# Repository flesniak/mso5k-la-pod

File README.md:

Original version by Flemming Frandsen: https://gitlab.com/dren.dk/mso5k-la-pod

```
MMMMMMMM               MMMMMMMM   SSSSSSSSSSSSSSS      OOOOOOOOO     555555555555555555 kkkkkkkk                            LLLLLLLLLLL                            AAA
M:::::::M             M:::::::M SS:::::::::::::::S   OO:::::::::OO   5::::::::::::::::5 k::::::k                            L:::::::::L                           A:::A
M::::::::M           M::::::::MS:::::SSSSSS::::::S OO:::::::::::::OO 5::::::::::::::::5 k::::::k                            L:::::::::L                          A:::::A
M:::::::::M         M:::::::::MS:::::S     SSSSSSSO:::::::OOO:::::::O5:::::555555555555 k::::::k                            LL:::::::LL                         A:::::::A
M::::::::::M       M::::::::::MS:::::S            O::::::O   O::::::O5:::::5             k:::::k    kkkkkkk                   L:::::L                          A:::::::::A
M:::::::::::M     M:::::::::::MS:::::S            O:::::O     O:::::O5:::::5             k:::::k   k:::::k                    L:::::L                         A:::::A:::::A
M:::::::M::::M   M::::M:::::::M S::::SSSS         O:::::O     O:::::O5:::::5555555555    k:::::k  k:::::k                     L:::::L                        A:::::A A:::::A
M::::::M M::::M M::::M M::::::M  SS::::::SSSSS    O:::::O     O:::::O5:::::::::::::::5   k:::::k k:::::k    ---------------   L:::::L                       A:::::A   A:::::A
M::::::M  M::::M::::M  M::::::M    SSS::::::::SS  O:::::O     O:::::O555555555555:::::5  k::::::k:::::k     -:::::::::::::-   L:::::L                      A:::::A     A:::::A
M::::::M   M:::::::M   M::::::M       SSSSSS::::S O:::::O     O:::::O            5:::::5 k:::::::::::k      ---------------   L:::::L                     A:::::AAAAAAAAA:::::A
M::::::M    M:::::M    M::::::M            S:::::SO:::::O     O:::::O            5:::::5 k:::::::::::k                        L:::::L                    A:::::::::::::::::::::A
M::::::M     MMMMM     M::::::M            S:::::SO::::::O   O::::::O5555555     5:::::5 k::::::k:::::k                       L:::::L         LLLLLL    A:::::AAAAAAAAAAAAA:::::A
M::::::M               M::::::MSSSSSSS     S:::::SO:::::::OOO:::::::O5::::::55555::::::5k::::::k k:::::k                    LL:::::::LLLLLLLLL:::::L   A:::::A             A:::::A
M::::::M               M::::::MS::::::SSSSSS:::::S OO:::::::::::::OO  55:::::::::::::55 k::::::k  k:::::k                   L::::::::::::::::::::::L  A:::::A               A:::::A
M::::::M               M::::::MS:::::::::::::::SS    OO:::::::::OO      55:::::::::55   k::::::k   k:::::k                  L::::::::::::::::::::::L A:::::A                 A:::::A
MMMMMMMM               MMMMMMMM SSSSSSSSSSSSSSS        OOOOOOOOO          555555555     kkkkkkkk    kkkkkkk                 LLLLLLLLLLLLLLLLLLLLLLLLAAAAAAA                   AAAAAAA
```

This is a reimplementation of the Logic Analyzer pod for the Rigol MSO5000 scopes.

The scopes all come with the ability to accept a logic analyzer, all that's needed is a probe, this project is the implementation of the probe.

The schematic and PCB is in kicad 5 format.

# Sub-projects

There are a number of different projects each in its own subdir:

## lmh7324-16ch

* All 16 channels on a single board
* Uses 4x LMH7324 comparators
* Shows threshold voltage of each 8ch bank

## lmh7324-8ch

* 8 channel frontend pod
* On a 4 layer board
* With lmh7324 comparators
* And a simple volt-meter that shows the threshold voltage.

## breakout
* Board for converting the 2x25 2.54 mm pitch connector on the scope to two 2x13 pin 1.27 mm pitch connectors.

## panel-2019-03-20

* Panel produced in march.

## voltmeter

The firmware for the micro controller

# Unfinished experiments

## lmh7322
* 16 channel frontend pod
* Pretty close clone of the original
* One-sided load
* On a 4 layer board
* Direct 2x50 2.54mm ribbon connector to the scope
* Status: Done, except for silkscreen

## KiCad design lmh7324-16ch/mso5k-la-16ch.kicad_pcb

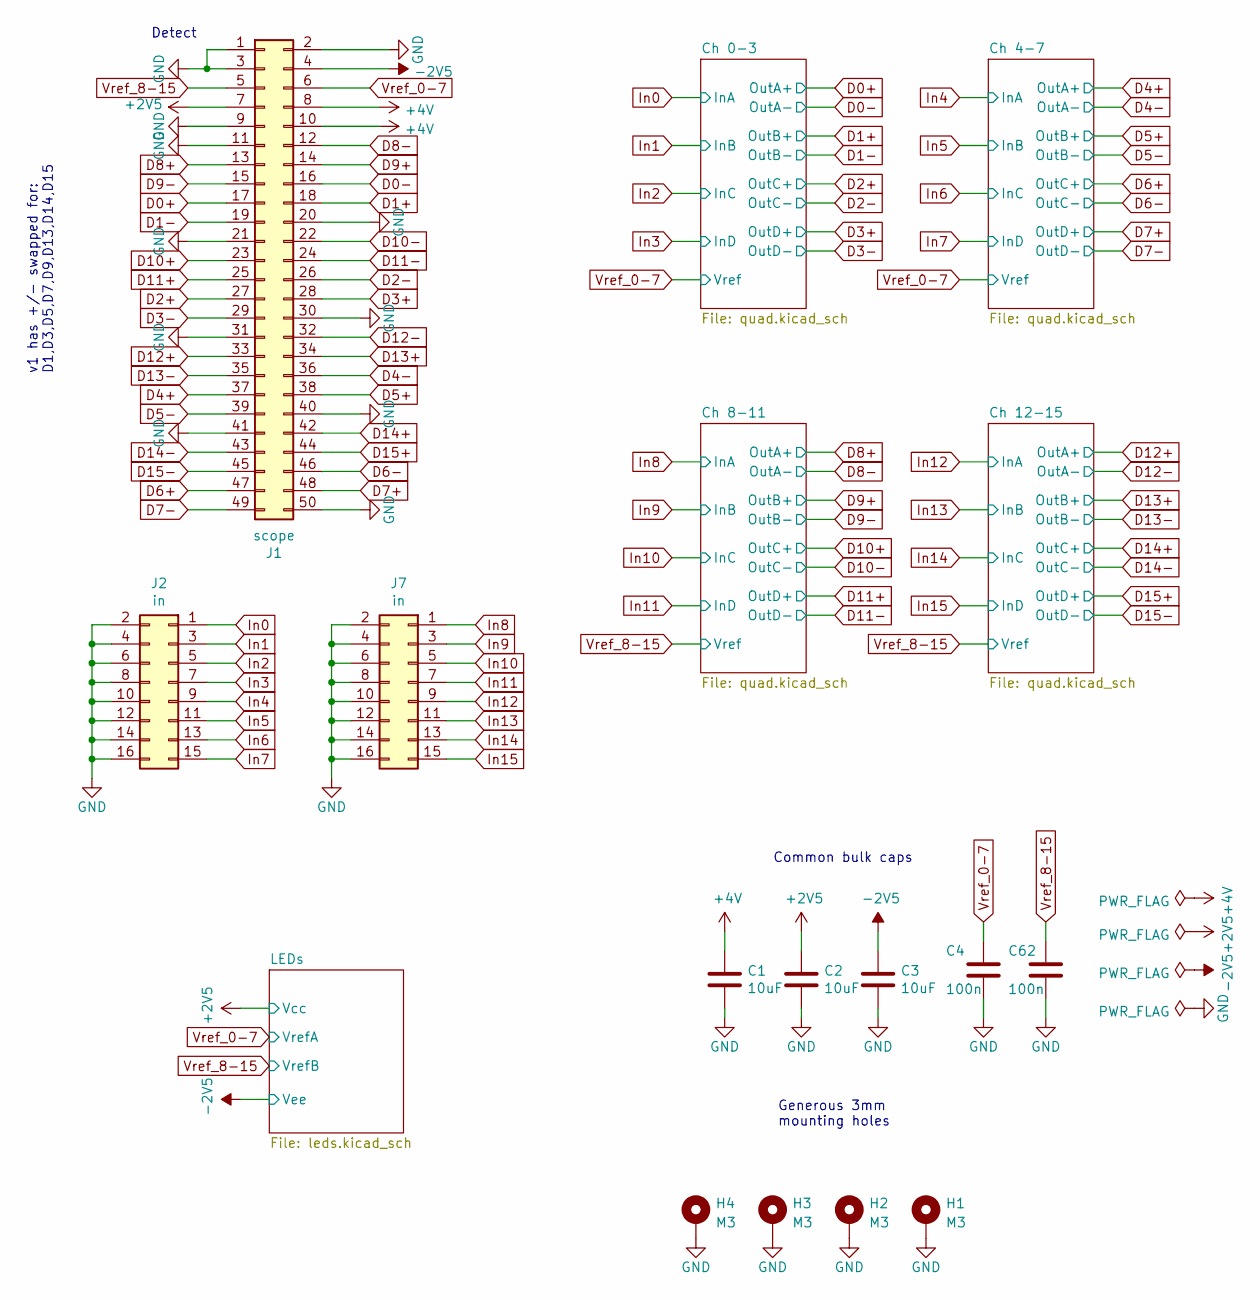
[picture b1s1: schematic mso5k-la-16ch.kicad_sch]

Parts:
C1, C2, C3: 10uF; C_0805_2012Metric
C4, C62: 100n; C_0603_1608Metric
H1, H2, H3, H4: M3; MountingHole_3.2mm_M3_Pad_Via
J1: scope; IDC-Header_2x25_P2.54mm_Vertical
J2, J7: in; PinSocket_2x08_P2.54mm_Vertical

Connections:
+2V5: C2.1, J1.7; also elsewhere on the board
+4V: C1.1, J1.8, J1.10; also elsewhere on the board
-2V5: C3.1, J1.4; also elsewhere on the board
D0+: J1.17; also elsewhere on the board
D0-: J1.16; also elsewhere on the board
D1+: J1.18; also elsewhere on the board
D1-: J1.19; also elsewhere on the board
D2+: J1.27; also elsewhere on the board
D2-: J1.26; also elsewhere on the board
D3+: J1.28; also elsewhere on the board
D3-: J1.29; also elsewhere on the board
D4+: J1.37; also elsewhere on the board
D4-: J1.36; also elsewhere on the board
D5+: J1.38; also elsewhere on the board
D5-: J1.39; also elsewhere on the board
D6+: J1.47; also elsewhere on the board
D6-: J1.46; also elsewhere on the board
D7+: J1.48; also elsewhere on the board
D7-: J1.49; also elsewhere on the board
D8+: J1.13; also elsewhere on the board
D8-: J1.12; also elsewhere on the board
D9+: J1.14; also elsewhere on the board
D9-: J1.15; also elsewhere on the board
D10+: J1.23; also elsewhere on the board
D10-: J1.22; also elsewhere on the board
D11+: J1.25; also elsewhere on the board
D11-: J1.24; also elsewhere on the board
D12+: J1.33; also elsewhere on the board
D12-: J1.32; also elsewhere on the board
D13+: J1.34; also elsewhere on the board
D13-: J1.35; also elsewhere on the board
D14+: J1.42; also elsewhere on the board
D14-: J1.43; also elsewhere on the board
D15+: J1.44; also elsewhere on the board
D15-: J1.45; also elsewhere on the board
GND: C1.2, C2.2, C3.2, C4.2, C62.2, H1.1, H2.1, H3.1, H4.1, J1.1, J1.2, J1.3, J1.9, J1.11, J1.20, J1.21, J1.30, J1.31, J1.40, J1.41, J1.50, J2.2, J2.4, J2.6, J2.8, J2.10, J2.12, J2.14, J2.16, J7.2, J7.4, J7.6, J7.8, J7.10, J7.12, J7.14, J7.16; also elsewhere on the board
In0: J2.1; also elsewhere on the board
In1: J2.3; also elsewhere on the board
In2: J2.5; also elsewhere on the board
In3: J2.7; also elsewhere on the board
In4: J2.9; also elsewhere on the board
In5: J2.11; also elsewhere on the board
In6: J2.13; also elsewhere on the board
In7: J2.15; also elsewhere on the board
In8: J7.1; also elsewhere on the board
In9: J7.3; also elsewhere on the board
In10: J7.5; also elsewhere on the board
In11: J7.7; also elsewhere on the board
In12: J7.9; also elsewhere on the board
In13: J7.11; also elsewhere on the board
In14: J7.13; also elsewhere on the board
In15: J7.15; also elsewhere on the board
Vref_0-7: C4.1, J1.6; also elsewhere on the board
Vref_8-15: C62.1, J1.5; also elsewhere on the board

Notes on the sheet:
Common bulk caps
v1 has +/- swapped for: D1,D3,D5,D7,D9,D13,D14,D15
Generous 3mm mounting holes
Detect

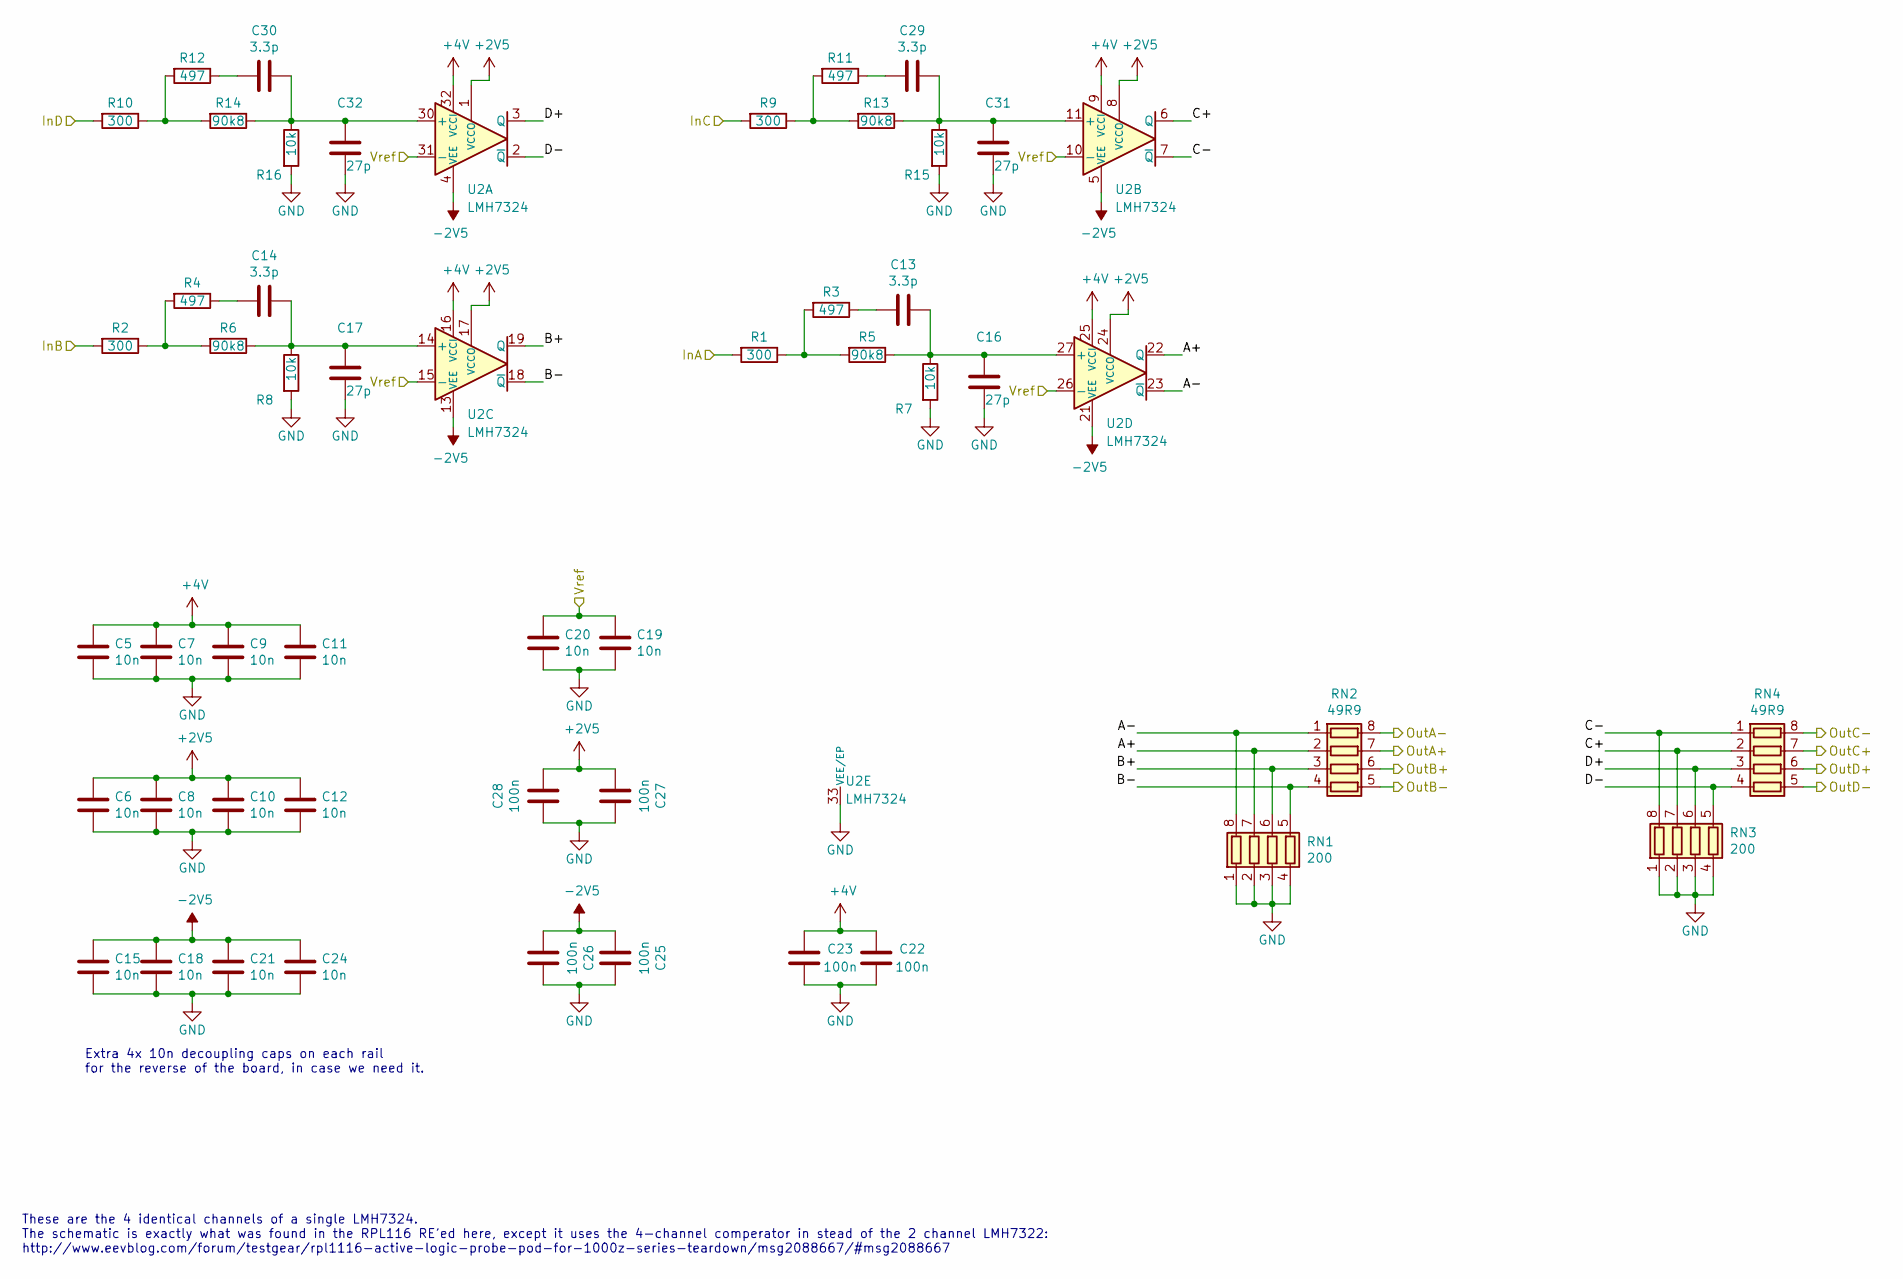
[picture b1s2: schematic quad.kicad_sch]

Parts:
C5, C6, C7, C8, C9, C10, C11, C12, C15, C18, C21, C24: 10n; C_0402_1005Metric
C13, C14, C29, C30: 3.3p; C_0603_1608Metric
C16, C17, C31, C32: 27p; C_0603_1608Metric
C19, C20: 10n; C_0603_1608Metric
C22, C23, C25, C26, C27, C28: 100n; C_0603_1608Metric
R1, R2, R9, R10: 300; R_0603_1608Metric
R3, R4, R11, R12: 497; R_0603_1608Metric
R5, R6, R13, R14: 90k8; R_0603_1608Metric
R7, R8, R15, R16: 10k; R_0603_1608Metric
RN1, RN3: 200; R_Array_Convex_4x0603
RN2, RN4: 49R9; R_Array_Convex_4x0603
U2: LMH7324; WQFN-32-1EP_5x5mm_P0.5mm_EP3.1x3.1mm

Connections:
+2V5: C6.1, C8.1, C10.1, C12.1, C27.2, C28.2, U2.1 (VCCO), U2.8 (VCCO), U2.17 (VCCO), U2.24 (VCCO); also elsewhere on the board
+4V: C5.1, C7.1, C9.1, C11.1, C22.1, C23.1, U2.9 (VCCI), U2.16 (VCCI), U2.25 (VCCI), U2.32 (VCCI); also elsewhere on the board
-2V5: C15.1, C18.1, C21.1, C24.1, C25.2, C26.2, U2.4 (VEE), U2.5 (VEE), U2.12 (VEE), U2.13 (VEE), U2.20 (VEE), U2.21 (VEE), U2.28 (VEE), U2.29 (VEE); also elsewhere on the board
/Ch 0-3/A+: RN1.7 (R2.2), RN2.2 (R2.1), U2.22 (Q)
/Ch 0-3/A-: RN1.8 (R1.2), RN2.1 (R1.1), U2.23 (~Q)
/Ch 0-3/B+: RN1.6 (R3.2), RN2.3 (R3.1), U2.19 (Q)
/Ch 0-3/B-: RN1.5 (R4.2), RN2.4 (R4.1), U2.18 (~Q)
/Ch 0-3/C+: RN3.7 (R2.2), RN4.2 (R2.1), U2.6 (Q)
/Ch 0-3/C-: RN3.8 (R1.2), RN4.1 (R1.1), U2.7 (~Q)
/Ch 0-3/D+: RN3.6 (R3.2), RN4.3 (R3.1), U2.3 (Q)
/Ch 0-3/D-: RN3.5 (R4.2), RN4.4 (R4.1), U2.2 (~Q)
D0+: RN2.7 (R2.2); also elsewhere on the board
D0-: RN2.8 (R1.2); also elsewhere on the board
D1+: RN2.6 (R3.2); also elsewhere on the board
D1-: RN2.5 (R4.2); also elsewhere on the board
D2+: RN4.7 (R2.2); also elsewhere on the board
D2-: RN4.8 (R1.2); also elsewhere on the board
D3+: RN4.6 (R3.2); also elsewhere on the board
D3-: RN4.5 (R4.2); also elsewhere on the board
GND: C5.2, C6.2, C7.2, C8.2, C9.2, C10.2, C11.2, C12.2, C15.2, C16.2, C17.2, C18.2, C19.2, C20.2, C21.2, C22.2, C23.2, C24.2, C25.1, C26.1, C27.1, C28.1, C31.2, C32.2, R7.2, R8.2, R15.2, R16.2, RN1.1 (R1.1), RN1.2 (R2.1), RN1.3 (R3.1), RN1.4 (R4.1), RN3.1 (R1.1), RN3.2 (R2.1), RN3.3 (R3.1), RN3.4 (R4.1), U2.33 (VEE/EP); also elsewhere on the board
In0: R1.2; also elsewhere on the board
In1: R2.2; also elsewhere on the board
In2: R9.2; also elsewhere on the board
In3: R10.2; also elsewhere on the board
unnamed: C13.2, R3.1
unnamed: C14.2, R4.1
unnamed: C29.2, R11.1
unnamed: C30.2, R12.1
unnamed: R1.1, R3.2, R5.2
unnamed: R2.1, R4.2, R6.2
unnamed: R10.1, R12.2, R14.2
unnamed: R9.1, R11.2, R13.2
unnamed: C30.1, C32.1, R14.1, R16.1, U2.30 (+)
unnamed: C29.1, C31.1, R13.1, R15.1, U2.11 (+)
unnamed: C14.1, C17.1, R6.1, R8.1, U2.14 (+)
unnamed: C13.1, C16.1, R5.1, R7.1, U2.27 (+)
Vref_0-7: C19.1, C20.1, U2.10 (-), U2.15 (-), U2.26 (-), U2.31 (-); also elsewhere on the board

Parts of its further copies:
C33, C34, C35, C36, C37, C38, C39, C40, C43, C46, C49, C52, C63, C64, C65, C66, C67, C68, C69, C70, C71, C74, C75, C76, C91, C92, C93, C94, C95, C96, C97, C98, C99, C102, C103, C104: 10n; C_0402_1005Metric
C41, C42, C57, C58, C72, C73, C87, C88, C100, C101, C115, C116: 3.3p; C_0603_1608Metric
C44, C45, C59, C60, C77, C78, C89, C90, C105, C106, C117, C118: 27p; C_0603_1608Metric
C47, C48, C79, C82, C107, C110: 10n; C_0603_1608Metric
C50, C51, C53, C54, C55, C56, C80, C81, C83, C84, C85, C86, C108, C109, C111, C112, C113, C114: 100n; C_0603_1608Metric
R17, R18, R25, R26, R38, R39, R46, R47, R54, R55, R62, R63: 300; R_0603_1608Metric
R19, R20, R27, R28, R40, R41, R48, R49, R56, R57, R64, R65: 497; R_0603_1608Metric
R21, R22, R29, R30, R42, R43, R50, R51, R58, R59, R66, R67: 90k8; R_0603_1608Metric
R23, R24, R31, R32, R44, R45, R52, R53, R60, R61, R68, R69: 10k; R_0603_1608Metric
RN5, RN7, RN9, RN11, RN13, RN15: 200; R_Array_Convex_4x0603
RN6, RN8, RN10, RN12, RN14, RN16: 49R9; R_Array_Convex_4x0603
U3, U4, U5: LMH7324; WQFN-32-1EP_5x5mm_P0.5mm_EP3.1x3.1mm

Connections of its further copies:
+2V5: C34.1, C36.1, C38.1, C40.1, C55.2, C56.2, C64.1, C67.1, C70.1, C75.1, C80.2, C83.2, C92.1, C95.1, C98.1, C103.1, C108.2, C111.2, U3.1 (VCCO), U3.8 (VCCO), U3.17 (VCCO), U3.24 (VCCO), U4.1 (VCCO), U4.8 (VCCO), U4.17 (VCCO), U4.24 (VCCO), U5.1 (VCCO), U5.8 (VCCO), U5.17 (VCCO), U5.24 (VCCO); also elsewhere on the board
+4V: C33.1, C35.1, C37.1, C39.1, C50.1, C51.1, C63.1, C66.1, C69.1, C74.1, C85.1, C86.1, C91.1, C94.1, C97.1, C102.1, C113.1, C114.1, U3.9 (VCCI), U3.16 (VCCI), U3.25 (VCCI), U3.32 (VCCI), U4.9 (VCCI), U4.16 (VCCI), U4.25 (VCCI), U4.32 (VCCI), U5.9 (VCCI), U5.16 (VCCI), U5.25 (VCCI), U5.32 (VCCI); also elsewhere on the board
-2V5: C43.1, C46.1, C49.1, C52.1, C53.2, C54.2, C65.1, C68.1, C71.1, C76.1, C81.2, C84.2, C93.1, C96.1, C99.1, C104.1, C109.2, C112.2, U3.4 (VEE), U3.5 (VEE), U3.12 (VEE), U3.13 (VEE), U3.20 (VEE), U3.21 (VEE), U3.28 (VEE), U3.29 (VEE), U4.4 (VEE), U4.5 (VEE), U4.12 (VEE), U4.13 (VEE), U4.20 (VEE), U4.21 (VEE), U4.28 (VEE), U4.29 (VEE), U5.4 (VEE), U5.5 (VEE), U5.12 (VEE), U5.13 (VEE), U5.20 (VEE), U5.21 (VEE), U5.28 (VEE), U5.29 (VEE); also elsewhere on the board
/Ch 4-7/A+: RN5.7 (R2.2), RN6.2 (R2.1), U3.22 (Q)
/Ch 4-7/A-: RN5.8 (R1.2), RN6.1 (R1.1), U3.23 (~Q)
/Ch 4-7/B+: RN5.6 (R3.2), RN6.3 (R3.1), U3.19 (Q)
/Ch 4-7/B-: RN5.5 (R4.2), RN6.4 (R4.1), U3.18 (~Q)
/Ch 4-7/C+: RN7.7 (R2.2), RN8.2 (R2.1), U3.6 (Q)
/Ch 4-7/C-: RN7.8 (R1.2), RN8.1 (R1.1), U3.7 (~Q)
/Ch 4-7/D+: RN7.6 (R3.2), RN8.3 (R3.1), U3.3 (Q)
/Ch 4-7/D-: RN7.5 (R4.2), RN8.4 (R4.1), U3.2 (~Q)
/Ch 8-11/A+: RN9.7 (R2.2), RN10.2 (R2.1), U4.22 (Q)
/Ch 8-11/A-: RN9.8 (R1.2), RN10.1 (R1.1), U4.23 (~Q)
/Ch 8-11/B+: RN9.6 (R3.2), RN10.3 (R3.1), U4.19 (Q)
/Ch 8-11/B-: RN9.5 (R4.2), RN10.4 (R4.1), U4.18 (~Q)
/Ch 8-11/C+: RN11.7 (R2.2), RN12.2 (R2.1), U4.6 (Q)
/Ch 8-11/C-: RN11.8 (R1.2), RN12.1 (R1.1), U4.7 (~Q)
/Ch 8-11/D+: RN11.6 (R3.2), RN12.3 (R3.1), U4.3 (Q)
/Ch 8-11/D-: RN11.5 (R4.2), RN12.4 (R4.1), U4.2 (~Q)
/Ch 12-15/A+: RN13.7 (R2.2), RN14.2 (R2.1), U5.22 (Q)
/Ch 12-15/A-: RN13.8 (R1.2), RN14.1 (R1.1), U5.23 (~Q)
/Ch 12-15/B+: RN13.6 (R3.2), RN14.3 (R3.1), U5.19 (Q)
/Ch 12-15/B-: RN13.5 (R4.2), RN14.4 (R4.1), U5.18 (~Q)
/Ch 12-15/C+: RN15.7 (R2.2), RN16.2 (R2.1), U5.6 (Q)
/Ch 12-15/C-: RN15.8 (R1.2), RN16.1 (R1.1), U5.7 (~Q)
/Ch 12-15/D+: RN15.6 (R3.2), RN16.3 (R3.1), U5.3 (Q)
/Ch 12-15/D-: RN15.5 (R4.2), RN16.4 (R4.1), U5.2 (~Q)
D4+: RN6.7 (R2.2); also elsewhere on the board
D4-: RN6.8 (R1.2); also elsewhere on the board
D5+: RN6.6 (R3.2); also elsewhere on the board
D5-: RN6.5 (R4.2); also elsewhere on the board
D6+: RN8.7 (R2.2); also elsewhere on the board
D6-: RN8.8 (R1.2); also elsewhere on the board
D7+: RN8.6 (R3.2); also elsewhere on the board
D7-: RN8.5 (R4.2); also elsewhere on the board
D8+: RN10.7 (R2.2); also elsewhere on the board
D8-: RN10.8 (R1.2); also elsewhere on the board
D9+: RN10.6 (R3.2); also elsewhere on the board
D9-: RN10.5 (R4.2); also elsewhere on the board
D10+: RN12.7 (R2.2); also elsewhere on the board
D10-: RN12.8 (R1.2); also elsewhere on the board
D11+: RN12.6 (R3.2); also elsewhere on the board
D11-: RN12.5 (R4.2); also elsewhere on the board
D12+: RN14.7 (R2.2); also elsewhere on the board
D12-: RN14.8 (R1.2); also elsewhere on the board
D13+: RN14.6 (R3.2); also elsewhere on the board
D13-: RN14.5 (R4.2); also elsewhere on the board
D14+: RN16.7 (R2.2); also elsewhere on the board
D14-: RN16.8 (R1.2); also elsewhere on the board
D15+: RN16.6 (R3.2); also elsewhere on the board
D15-: RN16.5 (R4.2); also elsewhere on the board
GND: C33.2, C34.2, C35.2, C36.2, C37.2, C38.2, C39.2, C40.2, C43.2, C44.2, C45.2, C46.2, C47.2, C48.2, C49.2, C50.2, C51.2, C52.2, C53.1, C54.1, C55.1, C56.1, C59.2, C60.2, C63.2, C64.2, C65.2, C66.2, C67.2, C68.2, C69.2, C70.2, C71.2, C74.2, C75.2, C76.2, C77.2, C78.2, C79.2, C80.1, C81.1, C82.2, C83.1, C84.1, C85.2, C86.2, C89.2, C90.2, C91.2, C92.2, C93.2, C94.2, C95.2, C96.2, C97.2, C98.2, C99.2, C102.2, C103.2, C104.2, C105.2, C106.2, C107.2, C108.1, C109.1, C110.2, C111.1, C112.1, C113.2, C114.2, C117.2, C118.2, R23.2, R24.2, R31.2, R32.2, R44.2, R45.2, R52.2, R53.2, R60.2, R61.2, R68.2, R69.2, RN5.1 (R1.1), RN5.2 (R2.1), RN5.3 (R3.1), RN5.4 (R4.1), RN7.1 (R1.1), RN7.2 (R2.1), RN7.3 (R3.1), RN7.4 (R4.1), RN9.1 (R1.1), RN9.2 (R2.1), RN9.3 (R3.1), RN9.4 (R4.1), RN11.1 (R1.1), RN11.2 (R2.1), RN11.3 (R3.1), RN11.4 (R4.1), RN13.1 (R1.1), RN13.2 (R2.1), RN13.3 (R3.1), RN13.4 (R4.1), RN15.1 (R1.1), RN15.2 (R2.1), RN15.3 (R3.1), RN15.4 (R4.1), U3.33 (VEE/EP), U4.33 (VEE/EP), U5.33 (VEE/EP); also elsewhere on the board
In4: R17.2; also elsewhere on the board
In5: R18.2; also elsewhere on the board
In6: R25.2; also elsewhere on the board
In7: R26.2; also elsewhere on the board
In8: R46.2; also elsewhere on the board
In9: R39.2; also elsewhere on the board
In10: R47.2; also elsewhere on the board
In11: R38.2; also elsewhere on the board
In12: R62.2; also elsewhere on the board
In13: R55.2; also elsewhere on the board
In14: R63.2; also elsewhere on the board
In15: R54.2; also elsewhere on the board
unnamed: C41.2, R19.1
unnamed: C42.2, R20.1
unnamed: C57.2, R27.1
unnamed: C58.2, R28.1
unnamed: C72.2, R40.1
unnamed: C73.2, R41.1
unnamed: C87.2, R48.1
unnamed: C88.2, R49.1
unnamed: C100.2, R56.1
unnamed: C101.2, R57.1
unnamed: C115.2, R64.1
unnamed: C116.2, R65.1
unnamed: R17.1, R19.2, R21.2
unnamed: R18.1, R20.2, R22.2
unnamed: R25.1, R27.2, R29.2
unnamed: R26.1, R28.2, R30.2
unnamed: R38.1, R40.2, R42.2
unnamed: R39.1, R41.2, R43.2
unnamed: R46.1, R48.2, R50.2
unnamed: R47.1, R49.2, R51.2
unnamed: R54.1, R56.2, R58.2
unnamed: R55.1, R57.2, R59.2
unnamed: R62.1, R64.2, R66.2
unnamed: R63.1, R65.2, R67.2
unnamed: C58.1, C60.1, R30.1, R32.1, U3.30 (+)
unnamed: C57.1, C59.1, R29.1, R31.1, U3.11 (+)
unnamed: C42.1, C45.1, R22.1, R24.1, U3.14 (+)
unnamed: C41.1, C44.1, R21.1, R23.1, U3.27 (+)
unnamed: C72.1, C77.1, R42.1, R44.1, U4.30 (+)
unnamed: C88.1, C90.1, R51.1, R53.1, U4.11 (+)
unnamed: C73.1, C78.1, R43.1, R45.1, U4.14 (+)
unnamed: C87.1, C89.1, R50.1, R52.1, U4.27 (+)
unnamed: C100.1, C105.1, R58.1, R60.1, U5.30 (+)
unnamed: C116.1, C118.1, R67.1, R69.1, U5.11 (+)
unnamed: C101.1, C106.1, R59.1, R61.1, U5.14 (+)
unnamed: C115.1, C117.1, R66.1, R68.1, U5.27 (+)
Vref_0-7: C47.1, C48.1, U3.10 (-), U3.15 (-), U3.26 (-), U3.31 (-); also elsewhere on the board
Vref_8-15: C79.1, C82.1, C107.1, C110.1, U4.10 (-), U4.15 (-), U4.26 (-), U4.31 (-), U5.10 (-), U5.15 (-), U5.26 (-), U5.31 (-); also elsewhere on the board

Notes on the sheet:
Extra 4x 10n decoupling caps on each rail for the reverse of the board, in case we need it.
These are the 4 identical channels of a single LMH7324. The schematic is exactly what was found in the RPL116 RE'ed here, except it uses the 4-channel comperator in stead of the 2 channel LMH7322: http://www.eevblog.com/forum/testgear/rpl1116-active-logic-probe-pod-for-1000z-series-teardown/msg2088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

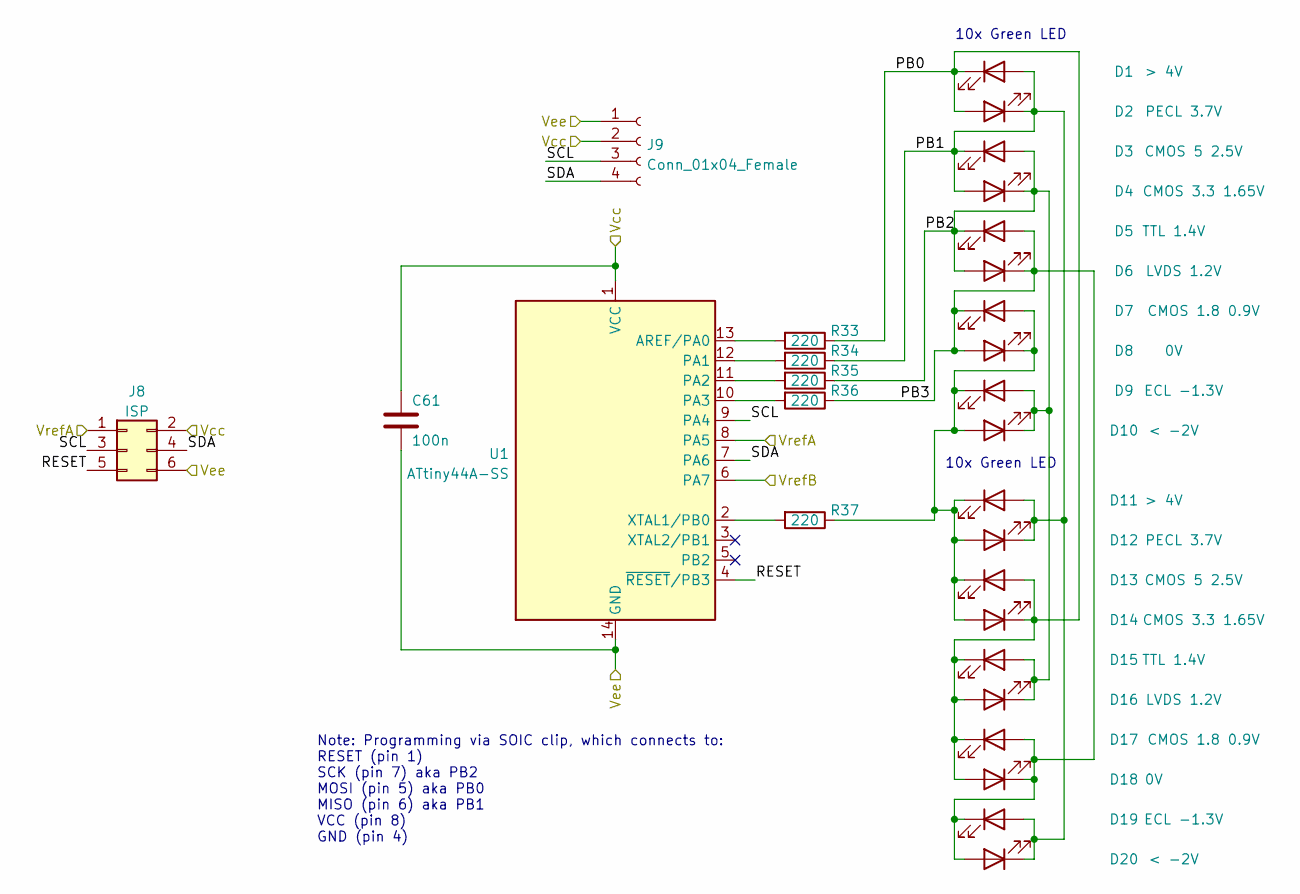
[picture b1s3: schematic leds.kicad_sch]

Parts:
C61: 100n; C_0603_1608Metric
D1, D11: > 4V; LED_0603_1608Metric
D2, D12: PECL 3.7V; LED_0603_1608Metric
D3, D13: CMOS 5 2.5V; LED_0603_1608Metric
D4, D14: CMOS 3.3 1.65V; LED_0603_1608Metric
D5, D15: TTL 1.4V; LED_0603_1608Metric
D6, D16: LVDS 1.2V; LED_0603_1608Metric
D7, D17: CMOS 1.8 0.9V; LED_0603_1608Metric
D8, D18: 0V; LED_0603_1608Metric
D9, D19: ECL -1.3V; LED_0603_1608Metric
D10, D20: < -2V; LED_0603_1608Metric
J8: ISP; PinHeader_2x03_P2.54mm_Vertical
J9: Conn_01x04_Female; PinHeader_1x04_P2.54mm_Vertical
R33, R34, R35, R36, R37: 220; R_0603_1608Metric
U1: ATtiny44A-SS; SOIC-14_3.9x8.7mm_P1.27mm

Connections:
+2V5: C61.1, J8.2, J9.2, U1.1 (VCC); also elsewhere on the board
-2V5: C61.2, J8.6, J9.1, U1.14 (GND); also elsewhere on the board
/LEDs/PB0: D1.1 (K), D2.2 (A), D13.2 (A), D14.1 (K), D15.1 (K), D16.2 (A), D17.1 (K), D18.2 (A), R33.1
/LEDs/PB1: D1.2 (A), D2.1 (K), D3.1 (K), D4.2 (A), D11.2 (A), D12.1 (K), D19.2 (A), D20.1 (K), R34.1
/LEDs/PB2: D3.2 (A), D4.1 (K), D5.1 (K), D6.2 (A), D9.2 (A), D10.1 (K), D15.2 (A), D16.1 (K), R35.1
/LEDs/PB3: D5.2 (A), D6.1 (K), D7.1 (K), D8.2 (A), D17.2 (A), D18.1 (K), D19.1 (K), D20.2 (A), R36.1
/LEDs/RESET: J8.5, U1.4 (~RESET/PB3)
/LEDs/SCL: J8.3, J9.3, U1.9 (PA4)
/LEDs/SDA: J8.4, J9.4, U1.7 (PA6)
unnamed: D7.2 (A), D8.1 (K), D9.1 (K), D10.2 (A), D11.1 (K), D12.2 (A), D13.1 (K), D14.2 (A), R37.1
unnamed: R33.2, U1.13 (AREF/PA0)
unnamed: R34.2, U1.12 (PA1)
unnamed: R35.2, U1.11 (PA2)
unnamed: R36.2, U1.10 (PA3)
unnamed: R37.2, U1.2 (XTAL1/PB0)
Vref_0-7: J8.1, U1.8 (PA5); also elsewhere on the board
Vref_8-15: U1.6 (PA7); also elsewhere on the board

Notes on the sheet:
Note: Programming via SOIC clip, which connects to: RESET (pin 1) SCK (pin 7) aka PB2 MOSI (pin 5) aka PB0 MISO (pin 6) aka PB1 VCC (pin 8) GND (pin 4)
10x Green LED

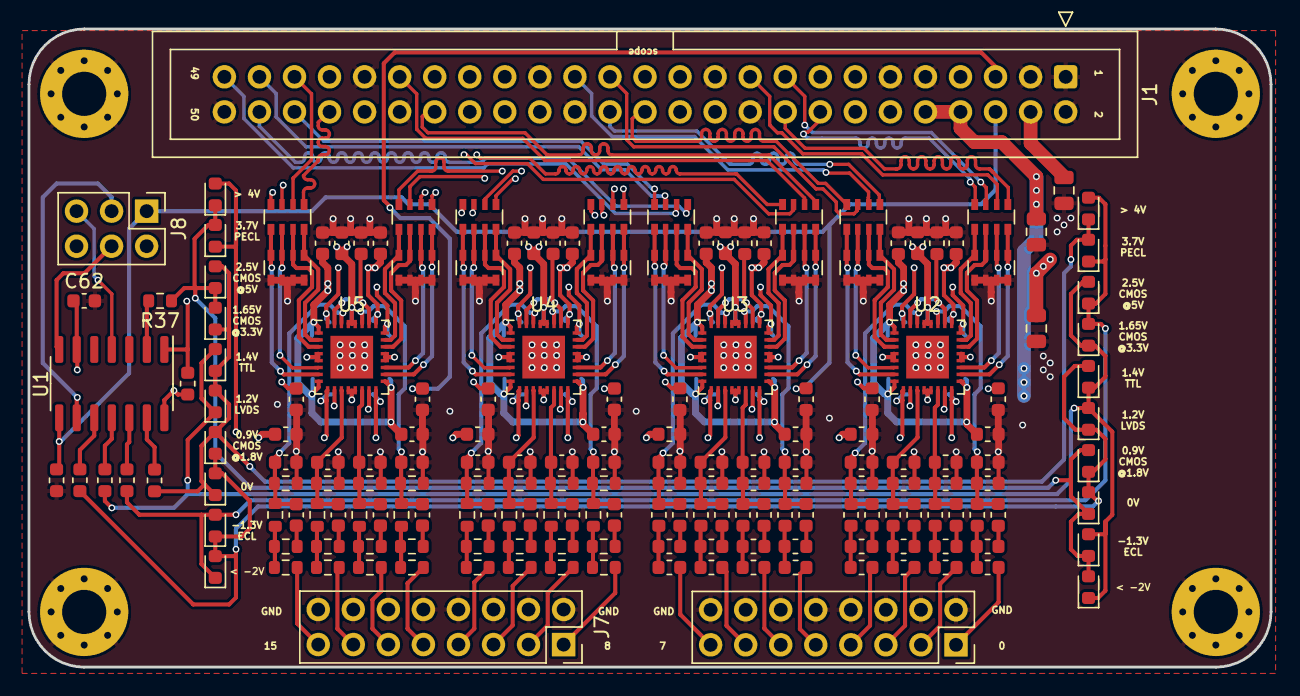
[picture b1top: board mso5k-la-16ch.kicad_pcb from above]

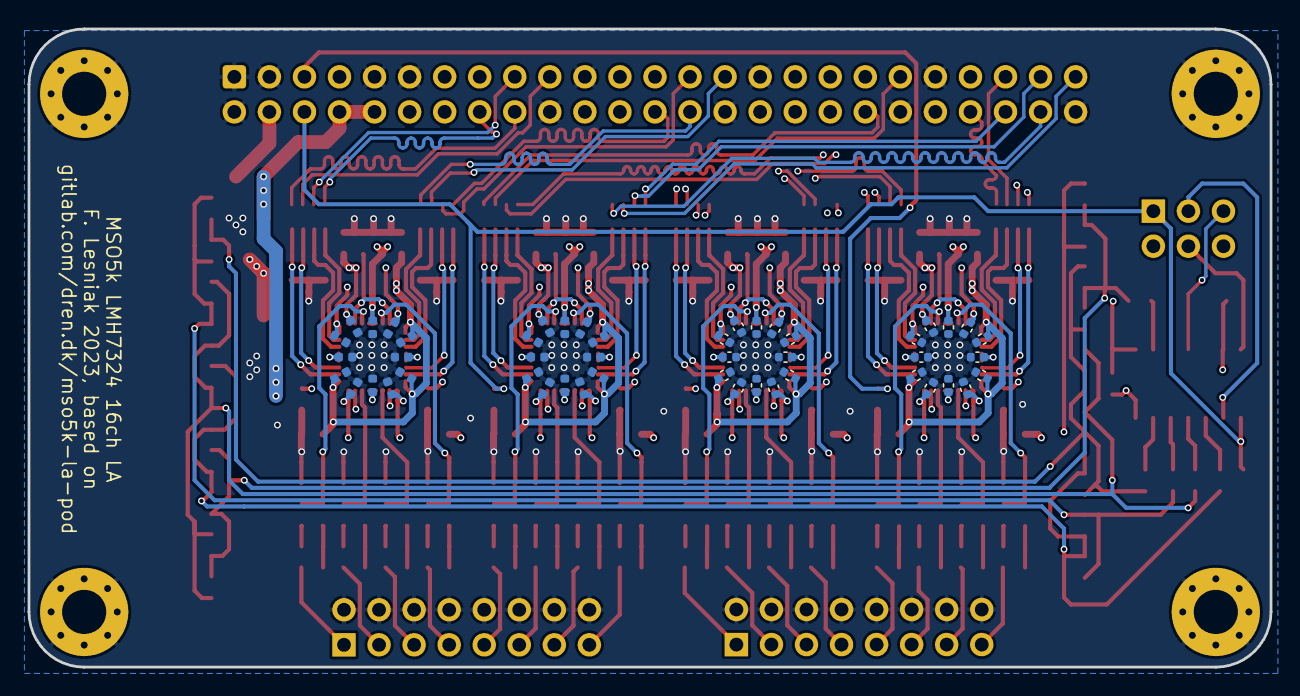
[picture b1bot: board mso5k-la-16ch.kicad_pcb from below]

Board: 4 copper layers, 90.0 x 46.2 mm, 236 parts (48 on the bottom side), 147 nets.

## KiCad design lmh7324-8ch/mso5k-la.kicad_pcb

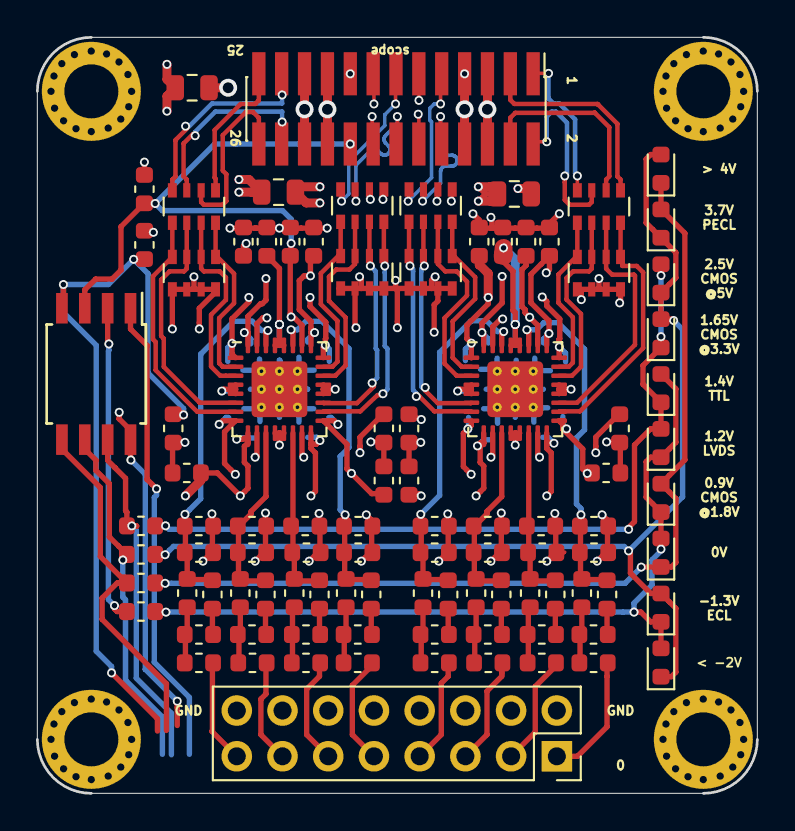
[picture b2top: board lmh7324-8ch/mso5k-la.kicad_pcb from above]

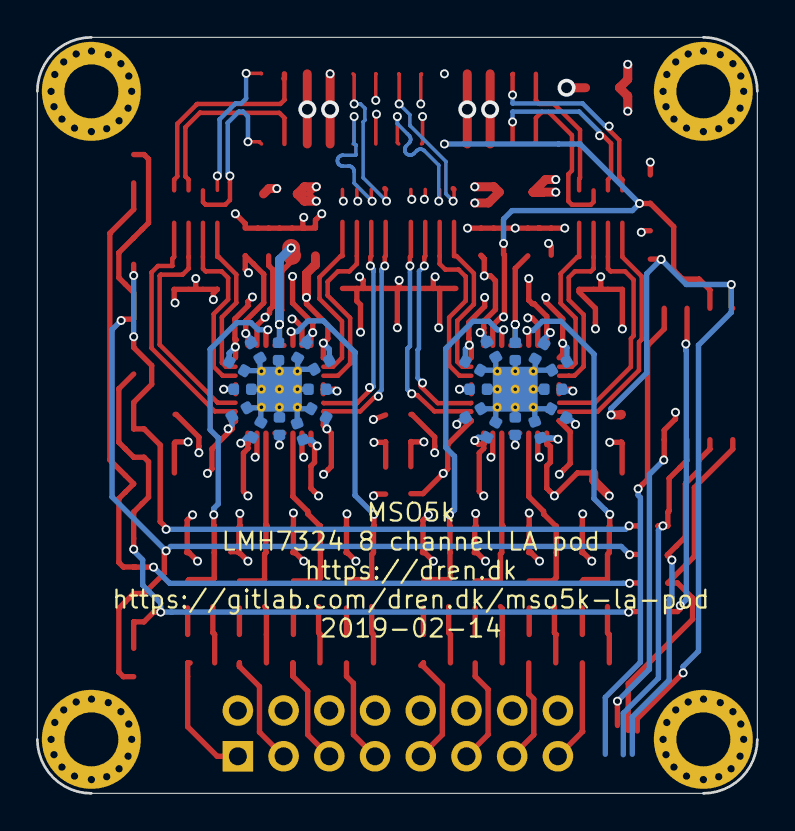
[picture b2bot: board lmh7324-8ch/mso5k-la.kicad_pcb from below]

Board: 4 copper layers, 40.0 x 42.0 mm, 124 parts (24 on the bottom side), 77 nets.

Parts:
C101, C102, C103: 10uF; C_0805_2012Metric
C104, C207, C208, C209, C210, C211, C212, C407, C408, C409, C410, C411, C412, C417: 100n; C_0603_1608Metric
C201, C202, C213, C214, C401, C402, C413, C414: 3.3p; C_0603_1608Metric
C203, C204, C215, C216, C403, C404, C415, C416: 27p; C_0603_1608Metric
C205, C206, C405, C406: 10n; C_0603_1608Metric
C217, C218, C219, C220, C221, C222, C223, C224, C225, C226, C227, C228, C301, C302, C303, C304, C305, C306, C307, C308, C309, C310, C311, C312: 10n; C_0402_1005Metric
D401: > 4V; LED_0603_1608Metric
D402: PECL 3.7V; LED_0603_1608Metric
D403: CMOS 5 2.5V; LED_0603_1608Metric
D404: CMOS 3.3 1.65V; LED_0603_1608Metric
D405: TTL 1.4V; LED_0603_1608Metric
D406: LVDS 1.2V; LED_0603_1608Metric
D407: CMOS 1.8 0.9V; LED_0603_1608Metric
D408: 0V; LED_0603_1608Metric
D409: ECL -1.3V; LED_0603_1608Metric
D410: < -2V; LED_0603_1608Metric
IC201, IC401: lmh7324; QFN-32-1EP_5x5mm_P0.5mm_EP3.1x3.1mm_ThermalVias
J101: out; PinHeader_2x13_P1.27mm_Vertical_SMD
J102: in; PinSocket_2x08_P2.54mm_Vertical
J103, J104, J105, J106: 3mm
R201, R202, R209, R210, R401, R402, R409, R410: 300; R_0603_1608Metric
R203, R204, R211, R212, R403, R404, R411, R412: 497; R_0603_1608Metric
R205, R206, R213, R214, R405, R406, R413, R414: 90k8; R_0603_1608Metric
R207, R208, R215, R216, R407, R408, R415, R416: 10k; R_0603_1608Metric
R418, R419, R420, R421: 220; R_0603_1608Metric
RN201, RN203, RN401, RN403: 200; R_Array_Convex_4x0603
RN202, RN204, RN402, RN404: 49R9; R_Array_Convex_4x0603
U401: ATtiny85-20SU; SOIJ-8_5.3x5.3mm_P1.27mm

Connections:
+2V5: C102.1, C211.2, C212.2, C218.1, C220.1, C222.1, C224.1, C302.1, C304.1, C306.1, C308.1, C411.2, C412.2, C417.1, IC201.1, IC201.8, IC201.17, IC201.24, IC401.1, IC401.8, IC401.17, IC401.24, J101.19, J101.20, U401.8
+4V: C101.1, C207.1, C208.1, C217.1, C219.1, C221.1, C223.1, C301.1, C303.1, C305.1, C307.1, C407.1, C408.1, IC201.9, IC201.16, IC201.25, IC201.32, IC401.9, IC401.16, IC401.25, IC401.32, J101.21, J101.22
-2V5: C103.1, C209.2, C210.2, C225.1, C226.1, C227.1, C228.1, C309.1, C310.1, C311.1, C312.1, C409.2, C410.2, C417.2, IC201.4, IC201.5, IC201.12, IC201.13, IC201.20, IC201.21, IC201.28, IC201.29, IC401.4, IC401.5, IC401.12, IC401.13, IC401.20, IC401.21, IC401.28, IC401.29, J101.5, J101.6, U401.4
/Ch 0-3/A+: IC401.22, RN401.7, RN402.2
/Ch 0-3/A-: IC401.23, RN401.8, RN402.1
/Ch 0-3/B+: IC401.19, RN401.6, RN402.3
/Ch 0-3/B-: IC401.18, RN401.5, RN402.4
/Ch 0-3/C+: IC401.6, RN403.7, RN404.2
/Ch 0-3/C-: IC401.7, RN403.8, RN404.1
/Ch 0-3/D+: IC401.3, RN403.6, RN404.3
/Ch 0-3/D-: IC401.2, RN403.5, RN404.4
/Ch 4-7/A+: IC201.22, RN201.7, RN202.2
/Ch 4-7/A-: IC201.23, RN201.8, RN202.1
/Ch 4-7/B+: IC201.19, RN201.6, RN202.3
/Ch 4-7/B-: IC201.18, RN201.5, RN202.4
/Ch 4-7/C+: IC201.6, RN203.7, RN204.2
/Ch 4-7/C-: IC201.7, RN203.8, RN204.1
/Ch 4-7/D+: IC201.3, RN203.6, RN204.3
/Ch 4-7/D-: IC201.2, RN203.5, RN204.4
/LEDs/PB0: D401.1, D402.2, D407.2, D408.1, R418.1
/LEDs/PB1: D401.2, D402.1, D403.1, D404.2, D409.2, D410.1, R419.1
/LEDs/PB2: D403.2, D404.1, D405.1, D406.2, R420.1
/LEDs/PB3: D405.2, D406.1, D407.1, D408.2, D409.1, D410.2, R421.1
D0+: J101.2, RN402.7
D0-: J101.1, RN402.8
D1+: J101.4, RN402.6
D1-: J101.3, RN402.5
D2+: J101.10, RN404.7
D2-: J101.9, RN404.8
D3+: J101.12, RN404.6
D3-: J101.11, RN404.5
D4+: J101.14, RN202.7
D4-: J101.13, RN202.8
D5+: J101.16, RN202.6
D5-: J101.15, RN202.5
D6+: J101.24, RN204.7
D6-: J101.23, RN204.8
D7+: J101.26, RN204.6
D7-: J101.25, RN204.5
GND: C101.2, C102.2, C103.2, C104.2, C203.2, C204.2, C205.2, C206.2, C207.2, C208.2, C209.1, C210.1, C211.1, C212.1, C215.2, C216.2, C217.2, C218.2, C219.2, C220.2, C221.2, C222.2, C223.2, C224.2, C225.2, C226.2, C227.2, C228.2, C301.2, C302.2, C303.2, C304.2, C305.2, C306.2, C307.2, C308.2, C309.2, C310.2, C311.2, C312.2, C403.2, C404.2, C405.2, C406.2, C407.2, C408.2, C409.1, C410.1, C411.1, C412.1, C415.2, C416.2, IC201.33, IC401.33, J101.7, J101.8, J101.17, J102.2, J102.4, J102.6, J102.8, J102.10, J102.12, J102.14, J102.16, J103.1, J104.1, J105.1, J106.1, R207.2, R208.2, R215.2, R216.2, R407.2, R408.2, R415.2, R416.2, RN201.1, RN201.2, RN201.3, RN201.4, RN203.1, RN203.2, RN203.3, RN203.4, RN401.1, RN401.2, RN401.3, RN401.4, RN403.1, RN403.2, RN403.3, RN403.4
In0: J102.1, R401.2
In1: J102.3, R402.2
In2: J102.5, R409.2
In3: J102.7, R410.2
In4: J102.9, R201.2
In5: J102.11, R202.2
In6: J102.13, R209.2
In7: J102.15, R210.2
unnamed: C201.1, C203.1, IC201.27, R205.1, R207.1
unnamed: C201.2, R203.1
unnamed: C202.1, C204.1, IC201.14, R206.1, R208.1
unnamed: C202.2, R204.1
unnamed: C213.1, C215.1, IC201.11, R213.1, R215.1
unnamed: C213.2, R211.1
unnamed: C214.1, C216.1, IC201.30, R214.1, R216.1
unnamed: C214.2, R212.1
unnamed: C401.1, C403.1, IC401.27, R405.1, R407.1
unnamed: C401.2, R403.1
unnamed: C402.1, C404.1, IC401.14, R406.1, R408.1
unnamed: C402.2, R404.1
unnamed: C413.1, C415.1, IC401.11, R413.1, R415.1
unnamed: C413.2, R411.1
unnamed: C414.1, C416.1, IC401.30, R414.1, R416.1
unnamed: C414.2, R412.1
unnamed: R201.1, R203.2, R205.2
unnamed: R202.1, R204.2, R206.2
unnamed: R209.1, R211.2, R213.2
unnamed: R210.1, R212.2, R214.2
unnamed: R401.1, R403.2, R405.2
unnamed: R402.1, R404.2, R406.2
unnamed: R409.1, R411.2, R413.2
unnamed: R410.1, R412.2, R414.2
unnamed: R418.2, U401.5
unnamed: R419.2, U401.6
unnamed: R420.2, U401.7
unnamed: R421.2, U401.2
Vref: C104.1, C205.1, C206.1, C405.1, C406.1, IC201.10, IC201.15, IC201.26, IC201.31, IC401.10, IC401.15, IC401.26, IC401.31, J101.18, U401.3
